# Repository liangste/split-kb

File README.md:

# split-kb

This repo contains the hardware design files for a 105 key QMK/VIA enabled split keyboard. The design is inspired by [Keebio Sinc](https://keeb.io/collections/sinc) and [Split111](https://geekhack.org/index.php?topic=103449.0). Unlike Sinc, this keyboard contains a Southpaw numpad, and unlike Split111, the design of this keyboard is open-sourced.

The PCB is designed using KiCAD. Case files for a stacked acrylic case is designed using Shapr3D. You can find the KiCAD project in this `root` directory, DXF drawing files under `case design/v1`, and layout and VIA files in the `layout` directory.

My QMK repo's [split-kb](https://github.com/liangste/qmk_firmware/tree/split-kb) branch contains all the configuration files necessary to run QMK and VIA. This repo only contains hardware designs.

_________________

Finished keyboard with purple top layer, clear mid layers, and wrist rests made with Red Oak hardwood (stained with linseed oil).

Bottom layer showcasing a Elite-PI microcontroller and a TRRS jack for serial connection between the two halves.

A snapshot of the PCB design on KiCAD.

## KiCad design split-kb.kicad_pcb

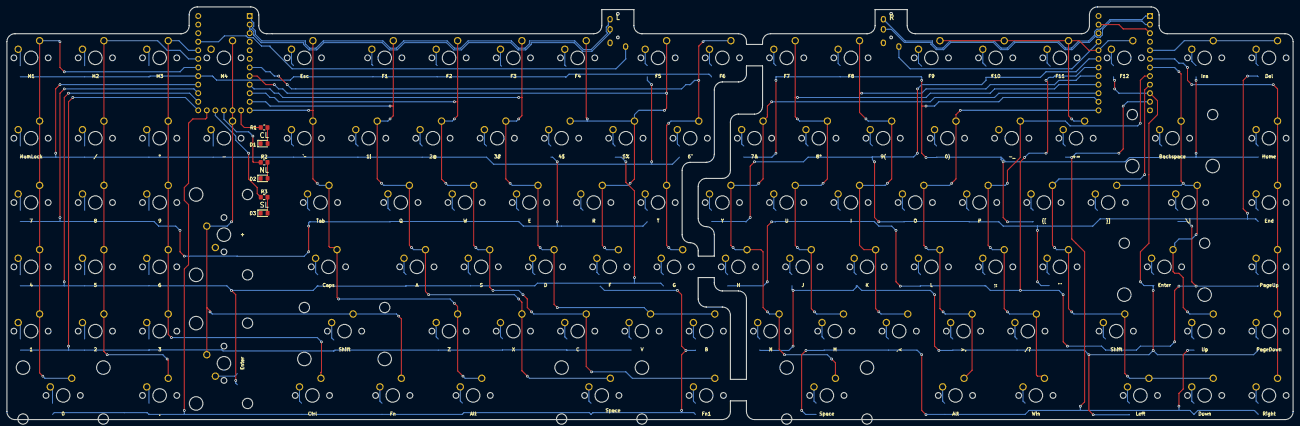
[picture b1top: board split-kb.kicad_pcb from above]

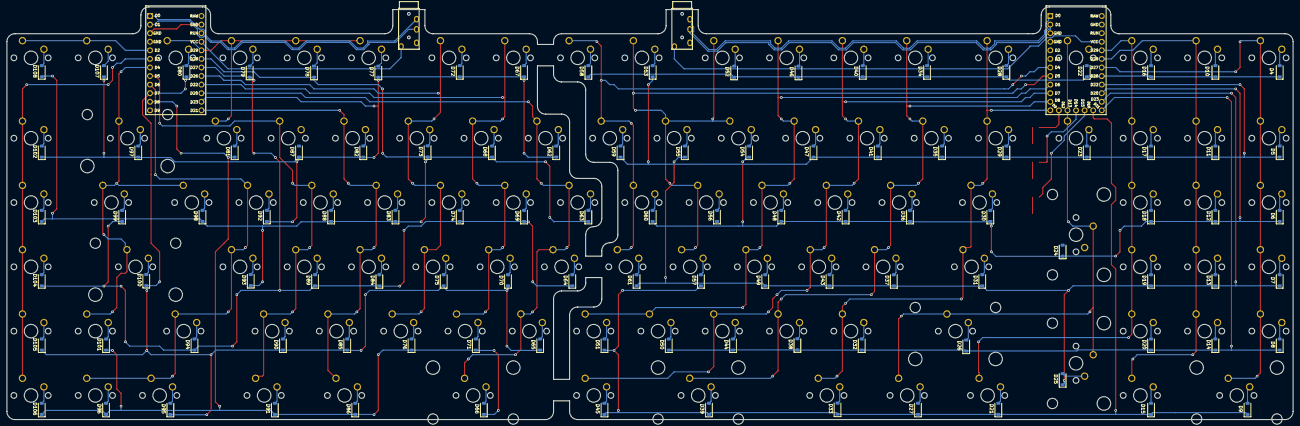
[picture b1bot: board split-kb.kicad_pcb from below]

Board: 2 copper layers, 381.0 x 122.2 mm, 220 parts (109 on the bottom side), 148 nets.

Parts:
D1, D2, D3: LED; LED_0805_2012Metric_Pad1.15x1.40mm_HandSolder
D4, D5, D6, D7, D8, D9, D10, D11, D12, D13, D14, D15, D16, D17, D18, D19, D20, D21, D22, D23, D24, D25, D26, D27, D28, D29, D30, D31, D32, D33, D34, D35, D36, D37, D38, D39, D40, D41, D42, D43, D44, D45, D46, D47, D48, D49, D50, D51, D52, D53, D54, D55, D56, D57, D58, D59, D60, D61, D62, D63, D64, D65, D66, D67, D68, D69, D70, D71, D72, D73, D74, D75, D76, D77, D78, D79, D80, D81, D82, D83, D84, D85, D86, D87, D88, D89, D90, D91, D92, D93, D94, D95, D96, D97, D98, D99, D100, D101, D102, D103, D104, D105, D106, D107, D108: D_Small; D_SOD-123
MX1: M1; Custom_SW_Cherry_MX_1.00u_PCB
MX2: NumLock; Custom_SW_Cherry_MX_1.00u_PCB
MX3: 7; Custom_SW_Cherry_MX_1.00u_PCB
MX4: 4; Custom_SW_Cherry_MX_1.00u_PCB
MX5: 1; Custom_SW_Cherry_MX_1.00u_PCB
MX6: 0; Custom_SW_Cherry_MX_2.00u_PCB_stabflip
MX7: M2; Custom_SW_Cherry_MX_1.00u_PCB
MX8: /; Custom_SW_Cherry_MX_1.00u_PCB
MX9: 8; Custom_SW_Cherry_MX_1.00u_PCB
MX10: 5; Custom_SW_Cherry_MX_1.00u_PCB
MX11: 2; Custom_SW_Cherry_MX_1.00u_PCB
MX12: .; Custom_SW_Cherry_MX_1.00u_PCB
MX13: M3; Custom_SW_Cherry_MX_1.00u_PCB
MX14: *; Custom_SW_Cherry_MX_1.00u_PCB
MX15: 9; Custom_SW_Cherry_MX_1.00u_PCB
MX16: 6; Custom_SW_Cherry_MX_1.00u_PCB
MX17: 3; Custom_SW_Cherry_MX_1.00u_PCB
MX18: Ctrl; Custom_SW_Cherry_MX_1.25u_PCB
MX19: M4; Custom_SW_Cherry_MX_1.00u_PCB
MX20: -; Custom_SW_Cherry_MX_1.00u_PCB
MX21: +; Custom_SW_Cherry_MX_2.00u_PCB_stabflip
MX22: Enter; Custom_SW_Cherry_MX_2.00u_PCB_stabflip
MX23: Shift; Custom_SW_Cherry_MX_2.25u_PCB
MX24: Fn; Custom_SW_Cherry_MX_1.25u_PCB
MX25: Esc; Custom_SW_Cherry_MX_1.00u_PCB
MX26: `~; Custom_SW_Cherry_MX_1.00u_PCB
MX27: Tab; Custom_SW_Cherry_MX_1.50u_PCB
MX28: Caps; Custom_SW_Cherry_MX_1.75u_PCB
MX29: Z; Custom_SW_Cherry_MX_1.00u_PCB
MX30, MX83: Alt; Custom_SW_Cherry_MX_1.25u_PCB
MX31: F1; Custom_SW_Cherry_MX_1.00u_PCB
MX32: 1!; Custom_SW_Cherry_MX_1.00u_PCB
MX33: Q; Custom_SW_Cherry_MX_1.00u_PCB
MX34: A; Custom_SW_Cherry_MX_1.00u_PCB
MX35: X; Custom_SW_Cherry_MX_1.00u_PCB
MX36: Space; Custom_SW_Cherry_MX_2.25u_PCB_stabflip
MX37: F2; Custom_SW_Cherry_MX_1.00u_PCB
MX38: 2@; Custom_SW_Cherry_MX_1.00u_PCB
MX39: W; Custom_SW_Cherry_MX_1.00u_PCB
MX40: S; Custom_SW_Cherry_MX_1.00u_PCB
MX41: C; Custom_SW_Cherry_MX_1.00u_PCB
MX42: Fn1; Custom_SW_Cherry_MX_1.00u_PCB
MX43: F3; Custom_SW_Cherry_MX_1.00u_PCB
MX44: 3#; Custom_SW_Cherry_MX_1.00u_PCB
MX45: E; Custom_SW_Cherry_MX_1.00u_PCB
MX46: D; Custom_SW_Cherry_MX_1.00u_PCB
MX47: V; Custom_SW_Cherry_MX_1.00u_PCB
MX48: B; Custom_SW_Cherry_MX_1.00u_PCB
MX49: F4; Custom_SW_Cherry_MX_1.00u_PCB
MX50: F5; Custom_SW_Cherry_MX_1.00u_PCB
MX51: 4$; Custom_SW_Cherry_MX_1.00u_PCB
MX52: 5%; Custom_SW_Cherry_MX_1.00u_PCB
MX53: R; Custom_SW_Cherry_MX_1.00u_PCB
MX54: F; Custom_SW_Cherry_MX_1.00u_PCB
MX55: F6; Custom_SW_Cherry_MX_1.00u_PCB
MX56: 6^; Custom_SW_Cherry_MX_1.00u_PCB
MX57: T; Custom_SW_Cherry_MX_1.00u_PCB
MX58: G; Custom_SW_Cherry_MX_1.00u_PCB
MX59: 7&; Custom_SW_Cherry_MX_1.00u_PCB
MX60: Y; Custom_SW_Cherry_MX_1.00u_PCB
MX61: H; Custom_SW_Cherry_MX_1.00u_PCB
MX62: N; Custom_SW_Cherry_MX_1.00u_PCB
MX63: Space; Custom_SW_Cherry_MX_2.75u_PCB_stabflip
MX64: F7; Custom_SW_Cherry_MX_1.00u_PCB
MX65: 8*; Custom_SW_Cherry_MX_1.00u_PCB
MX66: U; Custom_SW_Cherry_MX_1.00u_PCB
MX67: J; Custom_SW_Cherry_MX_1.00u_PCB
MX68: M; Custom_SW_Cherry_MX_1.00u_PCB
MX69: F8; Custom_SW_Cherry_MX_1.00u_PCB
MX70: 9(; Custom_SW_Cherry_MX_1.00u_PCB
MX71: I; Custom_SW_Cherry_MX_1.00u_PCB
MX72: K; Custom_SW_Cherry_MX_1.00u_PCB
MX73: ,<; Custom_SW_Cherry_MX_1.00u_PCB
MX74: F9; Custom_SW_Cherry_MX_1.00u_PCB
MX75: F10; Custom_SW_Cherry_MX_1.00u_PCB
MX76: F11; Custom_SW_Cherry_MX_1.00u_PCB
MX77: F12; Custom_SW_Cherry_MX_1.00u_PCB
MX78: +=; Custom_SW_Cherry_MX_1.00u_PCB
MX79: 0); Custom_SW_Cherry_MX_1.00u_PCB
MX80: O; Custom_SW_Cherry_MX_1.00u_PCB
MX81: L; Custom_SW_Cherry_MX_1.00u_PCB
MX82: >.; Custom_SW_Cherry_MX_1.00u_PCB
MX84: -_; Custom_SW_Cherry_MX_1.00u_PCB
MX85: P; Custom_SW_Cherry_MX_1.00u_PCB
MX86: ;:; Custom_SW_Cherry_MX_1.00u_PCB
MX87: /?; Custom_SW_Cherry_MX_1.00u_PCB
MX88: Win; Custom_SW_Cherry_MX_1.25u_PCB
MX89: {[; Custom_SW_Cherry_MX_1.00u_PCB
MX90: "'; Custom_SW_Cherry_MX_1.00u_PCB
MX91: Shift; Custom_SW_Cherry_MX_1.75u_PCB
MX92: Left; Custom_SW_Cherry_MX_1.00u_PCB
MX93: Down; Custom_SW_Cherry_MX_1.00u_PCB
MX94: Backspace; Custom_SW_Cherry_MX_2.00u_PCB
MX95: }]; Custom_SW_Cherry_MX_1.00u_PCB
MX96: \|; Custom_SW_Cherry_MX_1.50u_PCB
MX97: Enter; Custom_SW_Cherry_MX_2.25u_PCB
MX98: Up; Custom_SW_Cherry_MX_1.00u_PCB
MX99: Home; Custom_SW_Cherry_MX_1.00u_PCB
MX100: End; Custom_SW_Cherry_MX_1.00u_PCB
MX101: PageUp; Custom_SW_Cherry_MX_1.00u_PCB
MX102: PageDown; Custom_SW_Cherry_MX_1.00u_PCB
MX103: Right; Custom_SW_Cherry_MX_1.00u_PCB
MX104: Ins; Custom_SW_Cherry_MX_1.00u_PCB
MX105: Del; Custom_SW_Cherry_MX_1.00u_PCB
R1, R2, R3: 2.2k; R_0805_2012Metric_Pad1.20x1.40mm_HandSolder
U1, U3: TRRS; TRRS-PJ-320A
U2: Elite-PI
U4: Elite-PI; Elite-PI_24pin

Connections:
+3.3V: U1.1 (SLEEVE), U2.21 (VCC), U3.1 (SLEEVE), U4.21 (VCC)
/left_pcb/col0: MX1.1 (COL), MX2.1 (COL), MX3.1 (COL), MX4.1 (COL), MX5.1 (COL), MX6.1 (COL), U2.18 (D27)
/left_pcb/col1: MX7.1 (COL), MX8.1 (COL), MX9.1 (COL), MX10.1 (COL), MX11.1 (COL), MX12.1 (COL), U2.19 (D28)
/left_pcb/col2: MX13.1 (COL), MX14.1 (COL), MX15.1 (COL), MX16.1 (COL), MX17.1 (COL), MX18.1 (COL), U2.20 (D29)
/left_pcb/col3: MX19.1 (COL), MX20.1 (COL), MX21.1 (COL), MX22.1 (COL), MX23.1 (COL), MX24.1 (COL), U2.26 (D13)
/left_pcb/col4: MX25.1 (COL), MX26.1 (COL), MX27.1 (COL), MX28.1 (COL), MX29.1 (COL), MX30.1 (COL), U2.12 (D9)
/left_pcb/col5: MX31.1 (COL), MX32.1 (COL), MX33.1 (COL), MX34.1 (COL), MX35.1 (COL), MX36.1 (COL), U2.11 (D8)
/left_pcb/col6: MX37.1 (COL), MX38.1 (COL), MX39.1 (COL), MX40.1 (COL), MX41.1 (COL), MX42.1 (COL), U2.10 (D7)
/left_pcb/col7: MX43.1 (COL), MX44.1 (COL), MX45.1 (COL), MX46.1 (COL), MX47.1 (COL), MX48.1 (COL), U2.9 (D6)
/left_pcb/col8: MX49.1 (COL), MX50.1 (COL), MX51.1 (COL), MX52.1 (COL), MX53.1 (COL), MX54.1 (COL), U2.8 (D5)
/left_pcb/col9: MX55.1 (COL), MX56.1 (COL), MX57.1 (COL), MX58.1 (COL), U2.7 (D4)
/left_pcb/led0: R1.1, U2.25 (D12)
/left_pcb/led1: R2.1, U2.27 (D14)
/left_pcb/led2: R3.1, U2.28 (D15)
/left_pcb/row0: D4.1 (K), D10.1 (K), D16.1 (K), D22.1 (K), D28.1 (K), D34.1 (K), D40.1 (K), D46.1 (K), D52.1 (K), D58.1 (K), U2.17 (D26)
/left_pcb/row1: D5.1 (K), D11.1 (K), D17.1 (K), D23.1 (K), D29.1 (K), D35.1 (K), D41.1 (K), D47.1 (K), D53.1 (K), D59.1 (K), U2.16 (D22)
/left_pcb/row2: D6.1 (K), D12.1 (K), D18.1 (K), D24.1 (K), D30.1 (K), D36.1 (K), D42.1 (K), D48.1 (K), D54.1 (K), D60.1 (K), U2.15 (D20)
/left_pcb/row3: D7.1 (K), D13.1 (K), D19.1 (K), D25.1 (K), D31.1 (K), D37.1 (K), D43.1 (K), D49.1 (K), D55.1 (K), D61.1 (K), U2.14 (D23)
/left_pcb/row4: D8.1 (K), D14.1 (K), D20.1 (K), D26.1 (K), D32.1 (K), D38.1 (K), D44.1 (K), D50.1 (K), D56.1 (K), U2.13 (D21)
/left_pcb/row5: D9.1 (K), D15.1 (K), D21.1 (K), D27.1 (K), D33.1 (K), D39.1 (K), D45.1 (K), D51.1 (K), D57.1 (K), U2.29 (D16)
/left_pcb/serial+: U1.4 (RING2), U2.1 (D0)
/left_pcb/serial-: U1.3 (RING1), U2.2 (D1)
/right_pcb/col0: MX59.1 (COL), MX60.1 (COL), MX61.1 (COL), MX62.1 (COL), MX63.1 (COL), U4.15 (D20)
/right_pcb/col1: MX64.1 (COL), MX65.1 (COL), MX66.1 (COL), MX67.1 (COL), MX68.1 (COL), U4.16 (D22)
/right_pcb/col2: MX69.1 (COL), MX70.1 (COL), MX71.1 (COL), MX72.1 (COL), MX73.1 (COL), U4.17 (D26)
/right_pcb/col3: MX74.1 (COL), MX75.1 (COL), MX76.1 (COL), MX77.1 (COL), MX78.1 (COL), U4.20 (D29)
/right_pcb/col4: MX79.1 (COL), MX80.1 (COL), MX81.1 (COL), MX82.1 (COL), MX83.1 (COL), U4.13 (D21)
/right_pcb/col5: MX84.1 (COL), MX85.1 (COL), MX86.1 (COL), MX87.1 (COL), MX88.1 (COL), U4.8 (D5)
/right_pcb/col6: MX89.1 (COL), MX90.1 (COL), MX91.1 (COL), MX92.1 (COL), MX93.1 (COL), U4.9 (D6)
/right_pcb/col7: MX94.1 (COL), MX95.1 (COL), MX96.1 (COL), MX97.1 (COL), MX98.1 (COL), U4.7 (D4)
/right_pcb/col8: MX99.1 (COL), MX100.1 (COL), MX101.1 (COL), MX102.1 (COL), MX103.1 (COL), U4.6 (D3)
/right_pcb/col9: MX104.1 (COL), MX105.1 (COL), U4.5 (D2)
/right_pcb/row0: D62.1 (K), D67.1 (K), D72.1 (K), D77.1 (K), D82.1 (K), D87.1 (K), D92.1 (K), D97.1 (K), D102.1 (K), D107.1 (K), U4.14 (D23)
/right_pcb/row1: D63.1 (K), D68.1 (K), D73.1 (K), D78.1 (K), D83.1 (K), D88.1 (K), D93.1 (K), D98.1 (K), D103.1 (K), D108.1 (K), U4.19 (D28)
/right_pcb/row2: D64.1 (K), D69.1 (K), D74.1 (K), D79.1 (K), D84.1 (K), D89.1 (K), D94.1 (K), D99.1 (K), D104.1 (K), U4.18 (D27)
/right_pcb/row3: D65.1 (K), D70.1 (K), D75.1 (K), D80.1 (K), D85.1 (K), D90.1 (K), D95.1 (K), D100.1 (K), D105.1 (K), U4.10 (D7)
/right_pcb/row4: D66.1 (K), D71.1 (K), D76.1 (K), D81.1 (K), D86.1 (K), D91.1 (K), D96.1 (K), D101.1 (K), D106.1 (K), U4.11 (D8)
/right_pcb/serial+: U3.4 (RING2), U4.1 (D0)
/right_pcb/serial-: U3.3 (RING1), U4.2 (D1)
GND: D1.1 (K), D2.1 (K), D3.1 (K), U1.2 (TIP), U2.3 (GND), U2.4 (GND), U2.23 (GND), U3.2 (TIP), U4.3 (GND), U4.4 (GND), U4.23 (GND)
unnamed: D1.2 (A), R1.2
unnamed: D2.2 (A), R2.2
unnamed: D3.2 (A), R3.2
unnamed: D4.2 (A), MX1.2 (ROW)
unnamed: D5.2 (A), MX2.2 (ROW)
unnamed: D6.2 (A), MX3.2 (ROW)
unnamed: D7.2 (A), MX4.2 (ROW)
unnamed: D8.2 (A), MX5.2 (ROW)
unnamed: D9.2 (A), MX6.2 (ROW)
unnamed: D10.2 (A), MX7.2 (ROW)
unnamed: D11.2 (A), MX8.2 (ROW)
unnamed: D12.2 (A), MX9.2 (ROW)
unnamed: D13.2 (A), MX10.2 (ROW)
unnamed: D14.2 (A), MX11.2 (ROW)
unnamed: D15.2 (A), MX12.2 (ROW)
unnamed: D16.2 (A), MX13.2 (ROW)
unnamed: D17.2 (A), MX14.2 (ROW)
unnamed: D18.2 (A), MX15.2 (ROW)
unnamed: D19.2 (A), MX16.2 (ROW)
unnamed: D20.2 (A), MX17.2 (ROW)
unnamed: D21.2 (A), MX18.2 (ROW)
unnamed: D22.2 (A), MX19.2 (ROW)
unnamed: D23.2 (A), MX20.2 (ROW)
unnamed: D24.2 (A), MX21.2 (ROW)
unnamed: D25.2 (A), MX22.2 (ROW)
unnamed: D26.2 (A), MX23.2 (ROW)
unnamed: D27.2 (A), MX24.2 (ROW)
unnamed: D28.2 (A), MX25.2 (ROW)
unnamed: D29.2 (A), MX26.2 (ROW)
unnamed: D30.2 (A), MX27.2 (ROW)
unnamed: D31.2 (A), MX28.2 (ROW)
unnamed: D32.2 (A), MX29.2 (ROW)
unnamed: D33.2 (A), MX30.2 (ROW)
unnamed: D34.2 (A), MX31.2 (ROW)
unnamed: D35.2 (A), MX32.2 (ROW)
unnamed: D36.2 (A), MX33.2 (ROW)
unnamed: D37.2 (A), MX34.2 (ROW)
unnamed: D38.2 (A), MX35.2 (ROW)
unnamed: D39.2 (A), MX36.2 (ROW)
unnamed: D40.2 (A), MX37.2 (ROW)
unnamed: D41.2 (A), MX38.2 (ROW)
unnamed: D42.2 (A), MX39.2 (ROW)
unnamed: D43.2 (A), MX40.2 (ROW)
unnamed: D44.2 (A), MX41.2 (ROW)
unnamed: D45.2 (A), MX42.2 (ROW)
unnamed: D46.2 (A), MX43.2 (ROW)
unnamed: D47.2 (A), MX44.2 (ROW)
unnamed: D48.2 (A), MX45.2 (ROW)
unnamed: D49.2 (A), MX46.2 (ROW)
unnamed: D50.2 (A), MX47.2 (ROW)
unnamed: D51.2 (A), MX48.2 (ROW)
unnamed: D52.2 (A), MX49.2 (ROW)
unnamed: D53.2 (A), MX50.2 (ROW)
unnamed: D54.2 (A), MX51.2 (ROW)
unnamed: D55.2 (A), MX52.2 (ROW)
unnamed: D56.2 (A), MX53.2 (ROW)
unnamed: D57.2 (A), MX54.2 (ROW)
unnamed: D58.2 (A), MX55.2 (ROW)
unnamed: D59.2 (A), MX56.2 (ROW)
unnamed: D60.2 (A), MX57.2 (ROW)
unnamed: D61.2 (A), MX58.2 (ROW)
unnamed: D62.2 (A), MX59.2 (ROW)
unnamed: D63.2 (A), MX60.2 (ROW)
unnamed: D64.2 (A), MX61.2 (ROW)
unnamed: D65.2 (A), MX62.2 (ROW)
unnamed: D66.2 (A), MX63.2 (ROW)
unnamed: D67.2 (A), MX64.2 (ROW)
unnamed: D68.2 (A), MX65.2 (ROW)
unnamed: D69.2 (A), MX66.2 (ROW)
unnamed: D70.2 (A), MX67.2 (ROW)
unnamed: D71.2 (A), MX68.2 (ROW)
unnamed: D72.2 (A), MX69.2 (ROW)
unnamed: D73.2 (A), MX70.2 (ROW)
unnamed: D74.2 (A), MX71.2 (ROW)
unnamed: D75.2 (A), MX72.2 (ROW)
unnamed: D76.2 (A), MX73.2 (ROW)
unnamed: D77.2 (A), MX74.2 (ROW)
unnamed: D78.2 (A), MX75.2 (ROW)
unnamed: D79.2 (A), MX76.2 (ROW)
unnamed: D80.2 (A), MX77.2 (ROW)
unnamed: D81.2 (A), MX78.2 (ROW)
unnamed: D82.2 (A), MX79.2 (ROW)
unnamed: D83.2 (A), MX80.2 (ROW)
unnamed: D84.2 (A), MX81.2 (ROW)
unnamed: D85.2 (A), MX82.2 (ROW)
unnamed: D86.2 (A), MX83.2 (ROW)
unnamed: D87.2 (A), MX84.2 (ROW)
unnamed: D88.2 (A), MX85.2 (ROW)
unnamed: D89.2 (A), MX86.2 (ROW)
unnamed: D90.2 (A), MX87.2 (ROW)
unnamed: D91.2 (A), MX88.2 (ROW)
unnamed: D92.2 (A), MX89.2 (ROW)
unnamed: D93.2 (A), MX90.2 (ROW)
unnamed: D94.2 (A), MX91.2 (ROW)
unnamed: D95.2 (A), MX92.2 (ROW)
unnamed: D96.2 (A), MX93.2 (ROW)
unnamed: D97.2 (A), MX94.2 (ROW)
unnamed: D98.2 (A), MX95.2 (ROW)
unnamed: D99.2 (A), MX96.2 (ROW)
unnamed: D100.2 (A), MX97.2 (ROW)
unnamed: D101.2 (A), MX98.2 (ROW)
unnamed: D102.2 (A), MX99.2 (ROW)
unnamed: D103.2 (A), MX100.2 (ROW)
unnamed: D104.2 (A), MX101.2 (ROW)
unnamed: D105.2 (A), MX102.2 (ROW)
unnamed: D106.2 (A), MX103.2 (ROW)
unnamed: D107.2 (A), MX104.2 (ROW)
unnamed: D108.2 (A), MX105.2 (ROW)

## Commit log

2023-04-02 start design of left PCB
2023-04-02 add external oscillators
2023-04-03 add submodules
2023-04-03 add switch matrix and JTAG port
2023-04-04 initial footprint assignments
2023-04-04 associate footprints
2023-04-05 switch layout
2023-04-06 left half layout
2023-04-07 bomb for the redesign
2023-04-07 progress
2023-04-07 layout complete
2023-04-08 add photo
2023-04-08 add layout JSON files
2023-05-02 begin redesign
2023-05-02 add custom footprint library to the project
2023-05-02 add flipped-stab footprints
2023-05-03 redesign complete
2023-05-03 v0.2 done
2023-05-18 start redesign for v0.3
2023-05-18 v0.3 routing done
2023-05-18 v0.3 done
2023-06-19 add more design files
